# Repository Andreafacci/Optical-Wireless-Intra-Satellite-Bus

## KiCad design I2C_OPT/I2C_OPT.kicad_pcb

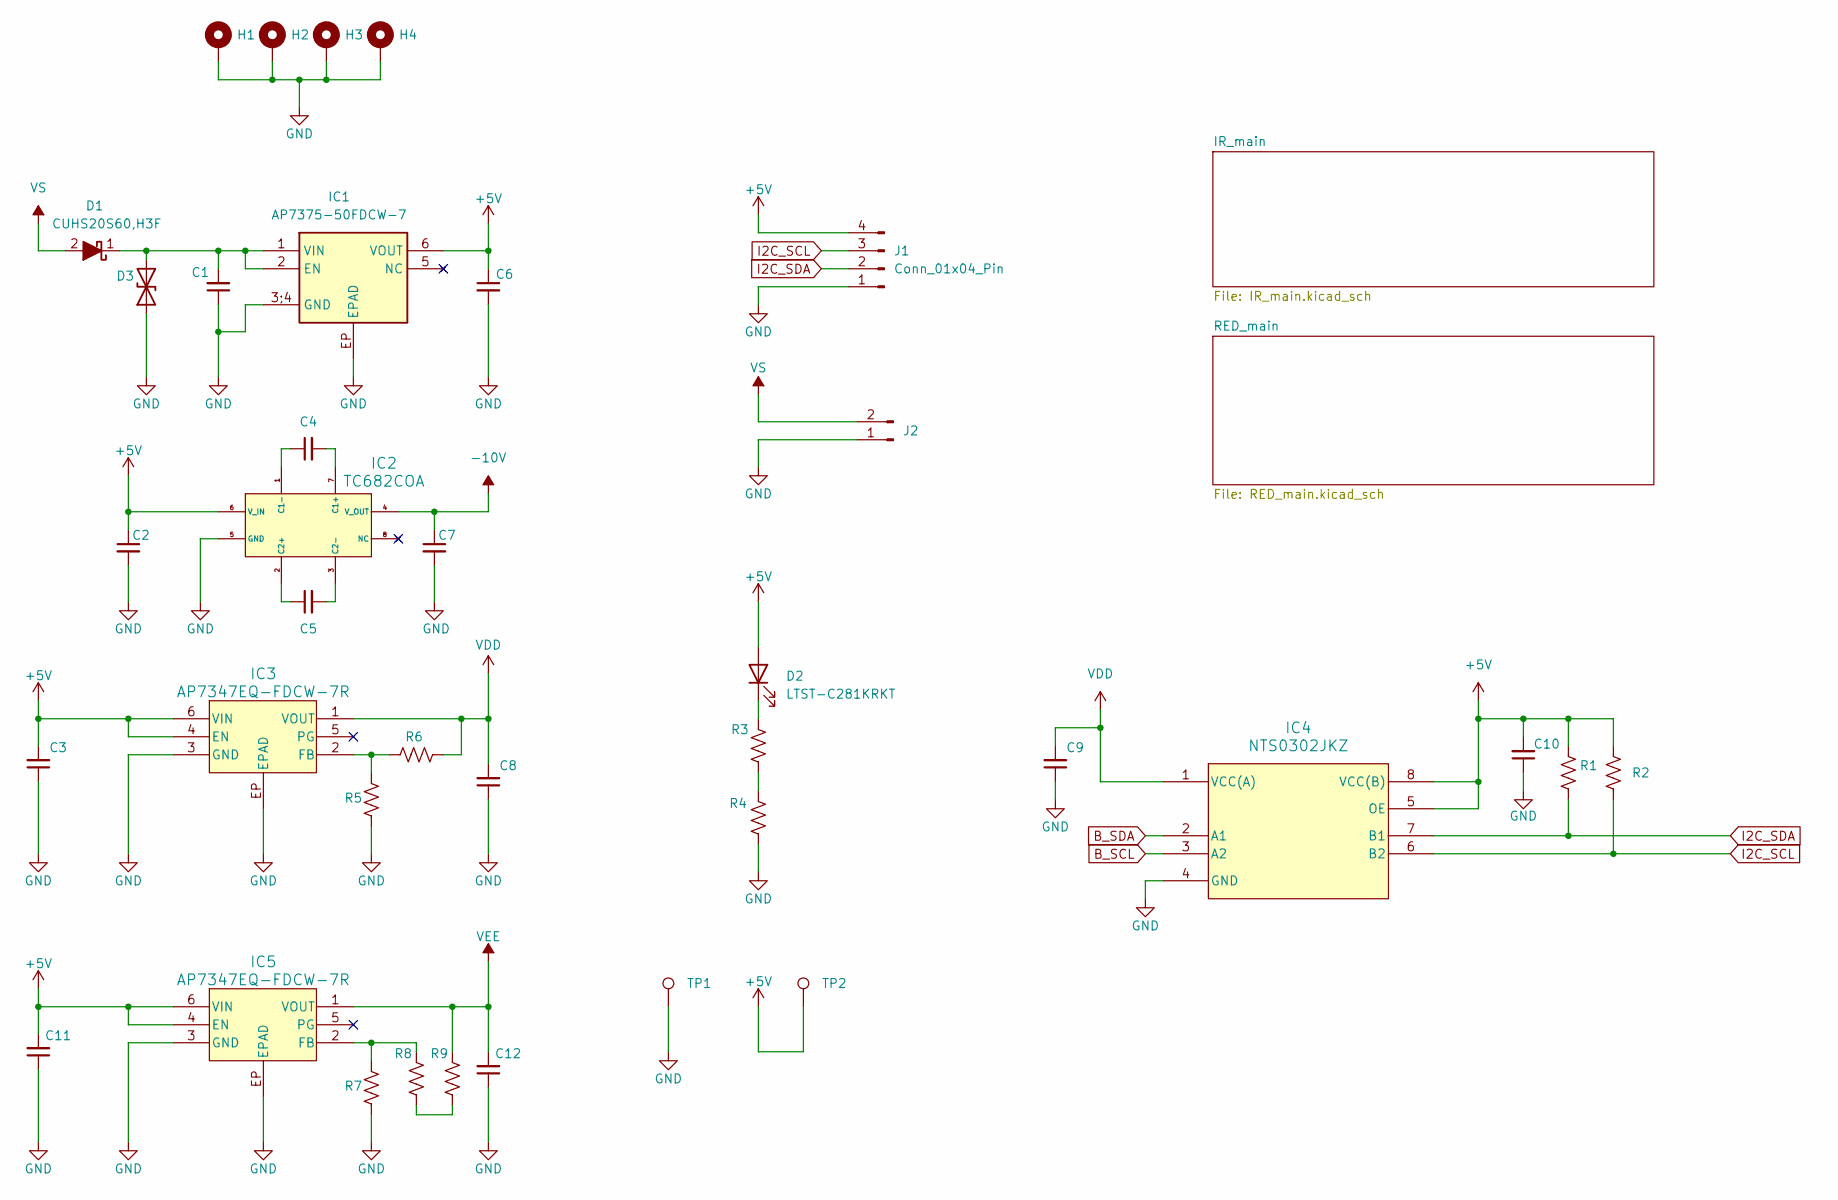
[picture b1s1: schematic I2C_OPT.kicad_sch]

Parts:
C1, C3, C4, C5, C8, C9, C10, C11, C12: C1005X5R1V105K050BC; C_0402_1005Metric
C2, C6, C7: CL10X106MO8NRNC; C_0603_1608Metric
D1: CUHS20S60,H3F; US2H; Mouser Part Number 757-CUHS20S60H3F
D2: LTST-C281KRKT; LED_0402_1005Metric
D3: 0402ESDA-MLP1; D_0402_1005Metric
H1, H2, H3, H4: MountingHole_Pad; MountingHole_2.2mm_M2_DIN965_Pad_TopBottom
IC1: AP7375-50FDCW-7; U-DFN2020-6; Mouser Part Number 621-AP7375-50FDCW-7
IC2: TC682COA; SOIC8-N_MC_MCH
IC3, IC5: AP7347EQ-FDCW-7R; U-DFN2020-6
IC4: NTS0302JKZ; X2SON08_1X1P4_NXP
J1: Conn_01x04_Pin; PinHeader_1x04_P2.54mm_Vertical
J2: PinHeader_1x02_P2.54mm_Vertical_GND
R1, R2: MCS0402MC1002FE000; R_0402_1005Metric
R3, R4: MCS04020D1200BE000; R_0402_1005Metric
R5: ERA-2AEB393X; R_0402_1005Metric
R6, R8, R9: ERA-2AEB8252X; R_0402_1005Metric
R7: MCS04020D4992BE000; R_0402_1005Metric
TP1, TP2: TestPoint; TestPoint_Pad_1.0x1.0mm

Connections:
+5V: C2.1, C3.2, C6.1, C10.2, C11.2, D2.2 (A), IC1.6 (VOUT), IC2.6 (V_IN), IC3.4 (EN), IC3.6 (VIN), IC4.5 (OE), IC4.8 (VCC(B)), IC5.4 (EN), IC5.6 (VIN), J1.4, R1.1, R2.1, TP2.1 (1_1); also elsewhere on the board
-10V: C7.1, IC2.4 (V_OUT); also elsewhere on the board
B_SCL: IC4.3 (A2); also elsewhere on the board
B_SDA: IC4.2 (A1); also elsewhere on the board
GND: C1.1, C2.2, C3.1, C6.2, C7.2, C8.1, C9.1, C10.1, C11.1, C12.1, D3.1 (A1), H1.1 (1_1), H2.1 (1_1), H3.1 (1_1), H4.1 (1_1), IC1.3 (GND), IC1.4 (GND), IC1.EP (EPAD), IC2.5 (GND), IC3.3 (GND), IC3.EP (EPAD), IC4.4 (GND), IC5.3 (GND), IC5.EP (EPAD), J1.1, J2.1, R4.1, R5.1, R7.1, TP1.1 (1_1); also elsewhere on the board
I2C_SCL: IC4.6 (B2), J1.3, R2.2
I2C_SDA: IC4.7 (B1), J1.2, R1.2
unnamed: C1.2, D1.1 (K), D3.2 (A2), IC1.1 (VIN), IC1.2 (EN)
unnamed: D2.1 (K), R3.2
unnamed: C4.2, IC2.7 (C1+)
unnamed: C4.1, IC2.1 (C1-)
unnamed: C5.1, IC2.2 (C2+)
unnamed: C5.2, IC2.3 (C2-)
unnamed: IC3.2 (FB), R5.2, R6.1
unnamed: IC5.2 (FB), R7.2, R8.2
unnamed: R3.1, R4.2
unnamed: R8.1, R9.1
VDD: C8.2, C9.2, IC3.1 (VOUT), IC4.1 (VCC(A)), R6.2
VEE: C12.2, IC5.1 (VOUT), R9.2; also elsewhere on the board
VS: D1.2 (A), J2.2

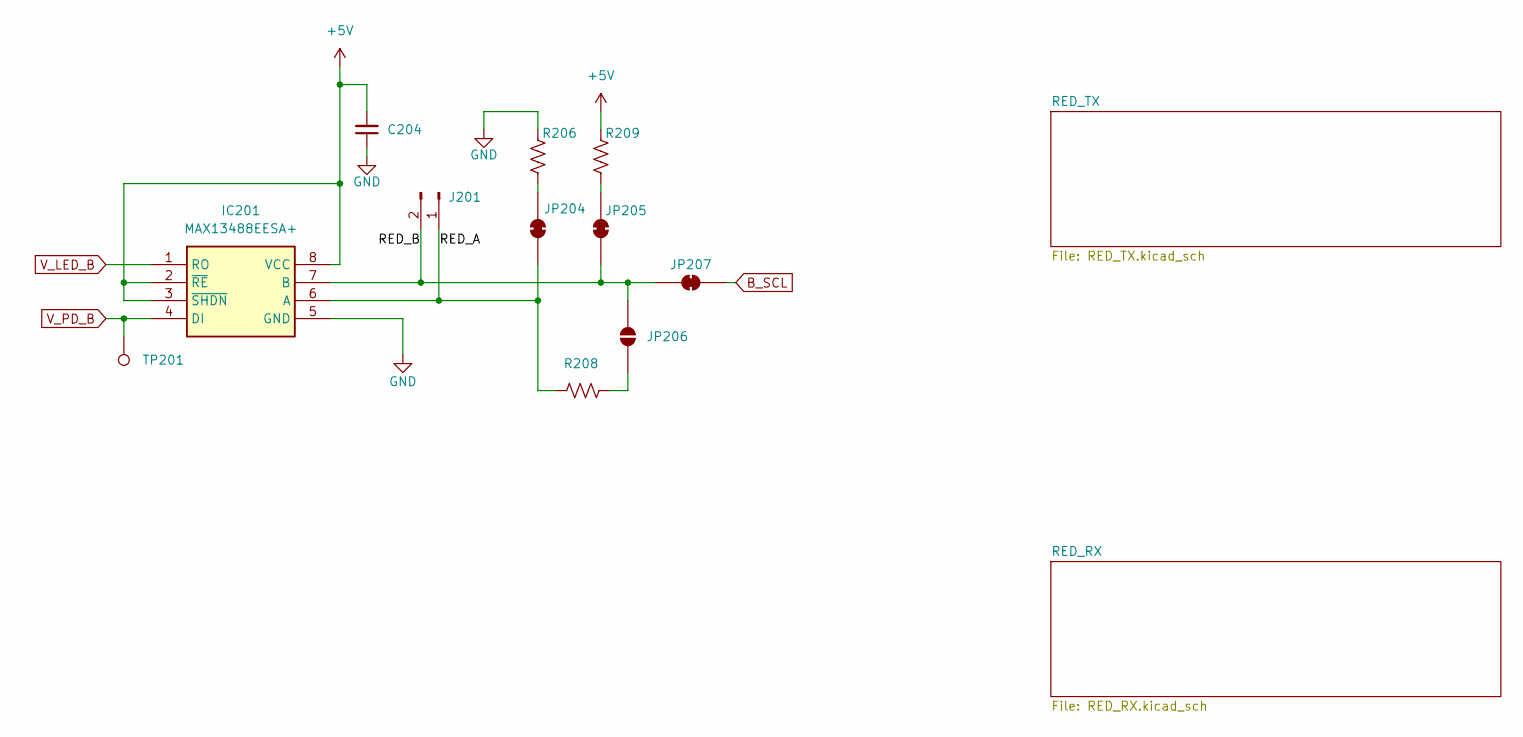
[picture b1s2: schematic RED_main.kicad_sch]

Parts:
C204: C1005X5R1V105K050BC; C_0402_1005Metric
IC201: MAX13488EESA+; SOIC127P600X175-8N; Mouser Part Number 700-MAX13488EESA
J201: PinHeader_1x02_P2.54mm_Vertical
JP204, JP205, JP207: SolderJumper_2_Bridged; SolderJumper-2_P1.3mm_Bridged_Pad1.0x1.5mm
JP206: SolderJumper_2_Open; SolderJumper-2_P1.3mm_Open_RoundedPad1.0x1.5mm
R206, R209: MCS04020C5601FE000; R_0402_1005Metric
R208: MCS04020D1200BE000; R_0402_1005Metric
TP201: TestPoint; TestPoint_Pad_1.0x1.0mm

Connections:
+5V: C204.2, IC201.2 (~RE), IC201.3 (~SHDN), IC201.8 (VCC), R209.1; also elsewhere on the board
/RED_main/RED_A: IC201.6 (A), J201.1, JP204.1 (A), R208.1
/RED_main/RED_B: IC201.7 (B), J201.2, JP205.1 (A), JP206.1 (A), JP207.2 (B)
B_SCL: JP207.1 (A); also elsewhere on the board
GND: C204.1, IC201.5 (GND), R206.1; also elsewhere on the board
unnamed: JP204.2 (B), R206.2
unnamed: JP205.2 (B), R209.2
unnamed: JP206.2 (B), R208.2
V_LED_B: IC201.1 (RO); also elsewhere on the board
V_PD_B: IC201.4 (DI), TP201.1 (1_1); also elsewhere on the board

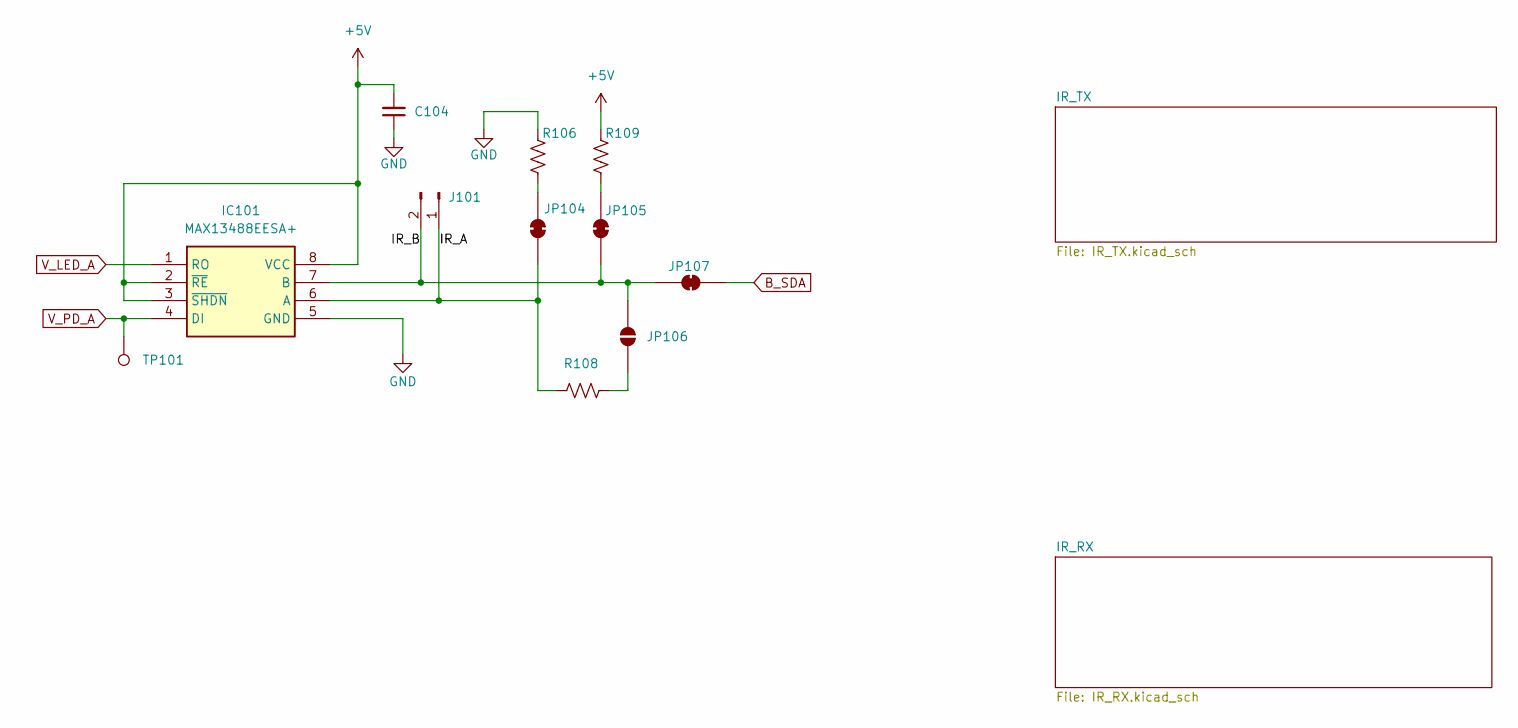
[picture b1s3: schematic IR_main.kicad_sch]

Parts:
C104: C1005X5R1V105K050BC; C_0402_1005Metric
IC101: MAX13488EESA+; SOIC127P600X175-8N; Mouser Part Number 700-MAX13488EESA
J101: PinHeader_1x02_P2.54mm_Vertical
JP104, JP105, JP107: SolderJumper_2_Bridged; SolderJumper-2_P1.3mm_Bridged_Pad1.0x1.5mm
JP106: SolderJumper_2_Open; SolderJumper-2_P1.3mm_Open_RoundedPad1.0x1.5mm
R106, R109: MCS04020C5601FE000; R_0402_1005Metric
R108: MCS04020D1200BE000; R_0402_1005Metric
TP101: TestPoint; TestPoint_Pad_1.0x1.0mm

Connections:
+5V: C104.2, IC101.2 (~RE), IC101.3 (~SHDN), IC101.8 (VCC), R109.1; also elsewhere on the board
/IR_main/IR_A: IC101.6 (A), J101.1, JP104.1 (A), R108.1
/IR_main/IR_B: IC101.7 (B), J101.2, JP105.1 (A), JP106.1 (A), JP107.2 (B)
B_SDA: JP107.1 (A); also elsewhere on the board
GND: C104.1, IC101.5 (GND), R106.1; also elsewhere on the board
unnamed: JP104.2 (B), R106.2
unnamed: JP105.2 (B), R109.2
unnamed: JP106.2 (B), R108.2
V_LED_A: IC101.1 (RO); also elsewhere on the board
V_PD_A: IC101.4 (DI), TP101.1 (1_1); also elsewhere on the board

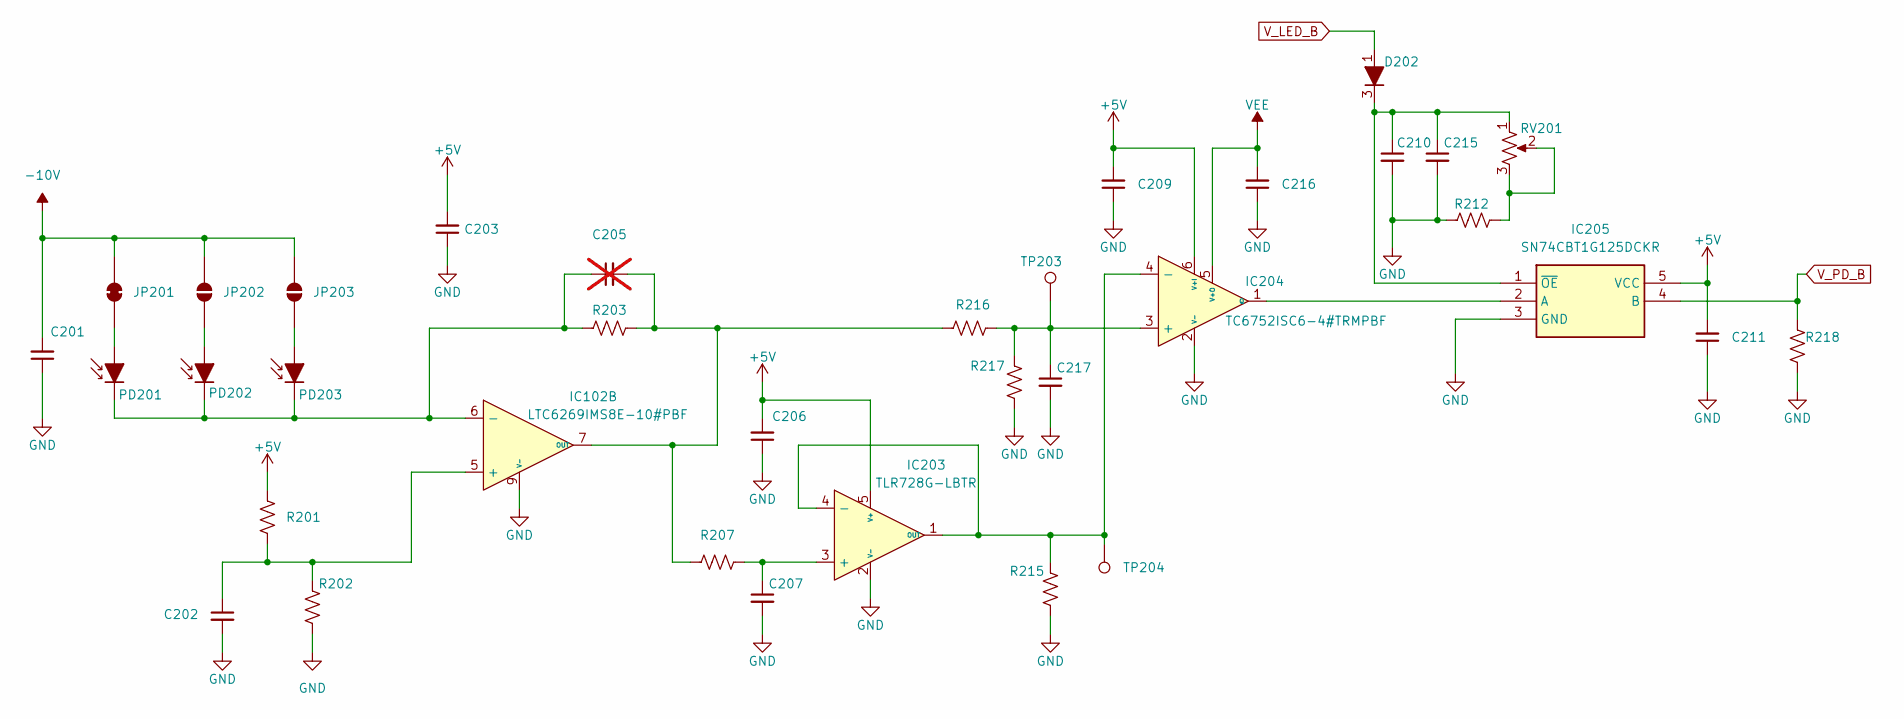
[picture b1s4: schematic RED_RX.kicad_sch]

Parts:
C201, C202, C203, C206, C209, C211, C216: C1005X5R1V105K050BC; C_0402_1005Metric
C205: 04023JR05ZBSTR\500; C_0402_1005Metric; not fitted
C207, C210, C215, C217: VJ0402A100FXACW1BC; C_0402_1005Metric
D202: 1SS193,LF; 1SS193LF; Mouser Part Number 757-1SS193LF
IC102: LTC6269IMS8E-10#PBF; SOP65P490X110-9N
IC203: TLR728G-LBTR; SOT23-5; Manufacturer_Part_Number TLR728G-LBTR
IC204: TC6752ISC6-4#TRMPBF; SC70-6; Mouser Part Number 584-LTC6752IS5TRMPBF
IC205: SN74CBT1G125DCKR; SOT65P210X110-5N; Mouser Part Number 595-SN74CBT1G125DBVR
JP201: SolderJumper_2_Bridged; SolderJumper-2_P1.3mm_Bridged_Pad1.0x1.5mm
JP202, JP203: SolderJumper_2_Open; SolderJumper-2_P1.3mm_Open_RoundedPad1.0x1.5mm
PD201: SFH 2240 A01; SFH2240A01
PD202: SFH 2713; SFH2713
PD203: SFH 2711 A01; SFH2711A01
R201, R203, R207: MCS04020C1004FE000; R_0402_1005Metric
R202, R215: MCS04020D4992BE000; R_0402_1005Metric
R212: MCS04020C5601FE000; R_0402_1005Metric
R216: MCS0402MC1002FE000; R_0402_1005Metric
R217: MCS04020C2703FE000
R218: ERA-2AEB8252X; R_0402_1005Metric
RV201: PVG5A204C03R00; PVG5A
TP203, TP204: TestPoint; TestPoint_Pad_1.0x1.0mm

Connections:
+5V: C203.2, C206.2, C209.2, C211.2, IC203.5 (V+), IC204.6 (V+I), IC205.5 (VCC), R201.2; also elsewhere on the board
-10V: C201.2, JP201.2 (B), JP202.2 (B), JP203.2 (B); also elsewhere on the board
GND: C201.1, C202.2, C203.1, C206.1, C207.2, C209.1, C210.2, C211.1, C215.2, C216.1, C217.2, IC102.9 (V-), IC203.2 (V-), IC204.2 (V-), IC205.3 (GND), R202.2, R212.1, R215.1, R217.2, R218.1; also elsewhere on the board
unnamed: C202.1, IC102.5 (+), R201.1, R202.1
unnamed: C205.1, IC102.6 (-), PD201.1 (K), PD202.1 (K), PD203.1 (K), R203.1
unnamed: C205.2, IC102.7 (OUT), R203.2, R207.2, R216.1
unnamed: C207.1, IC203.3 (+), R207.1
unnamed: IC203.1 (OUT), IC203.4 (-), IC204.4 (-), R215.2, TP204.1 (1_1)
unnamed: C217.1, IC204.3 (+), R216.2, R217.1, TP203.1 (1_1)
unnamed: IC204.1 (Q), IC205.2 (A)
unnamed: C210.1, C215.1, D202.3, IC205.1 (~OE), RV201.1
unnamed: JP201.1 (A), PD201.2 (A)
unnamed: JP202.1 (A), PD202.2 (A)
unnamed: JP203.1 (A), PD203.2 (A)
unnamed: R212.2, RV201.2, RV201.3
VEE: C216.2, IC204.5 (V+O); also elsewhere on the board
V_LED_B: D202.1; also elsewhere on the board
V_PD_B: IC205.4 (B), R218.2; also elsewhere on the board

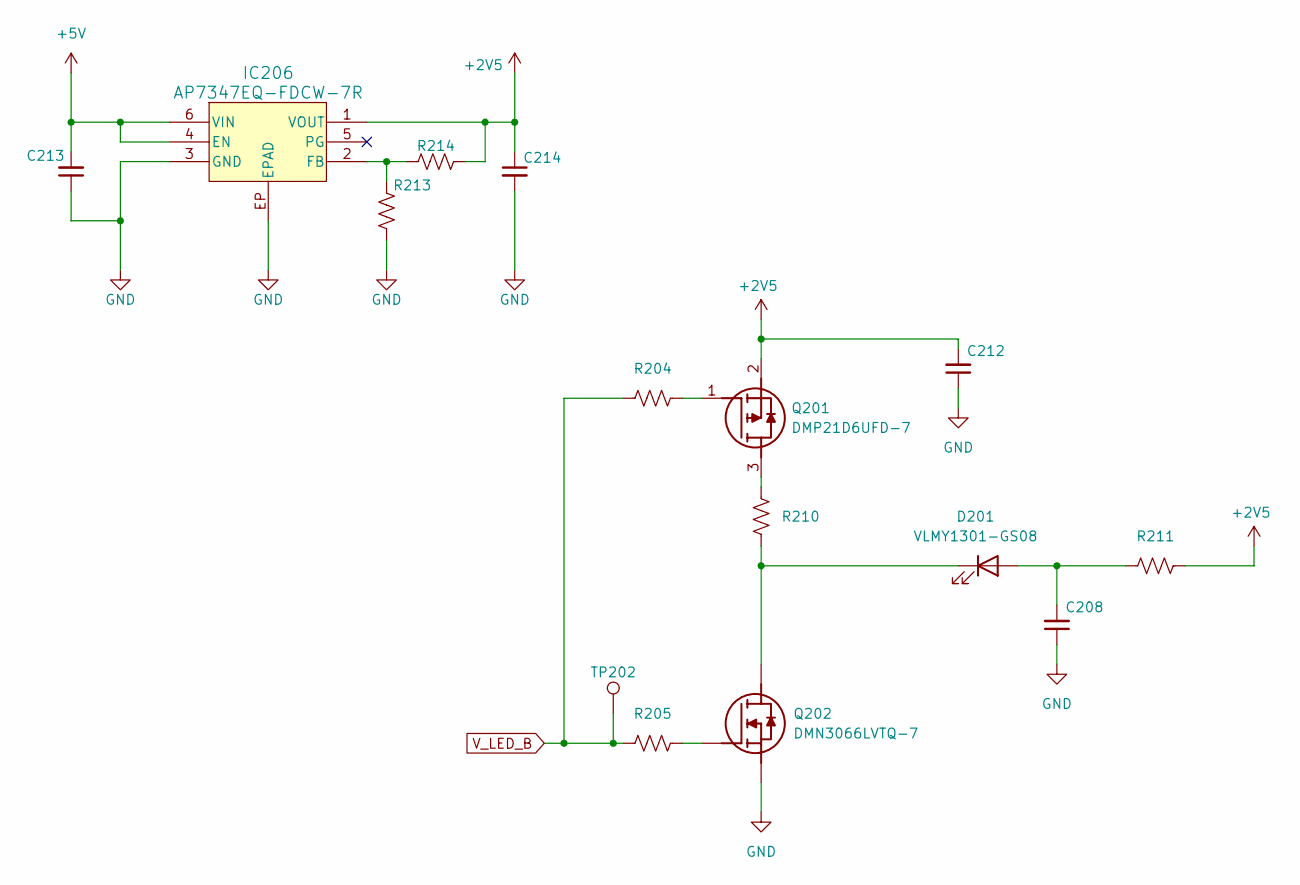
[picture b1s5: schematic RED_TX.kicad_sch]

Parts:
C208, C212, C213: C1005X5R1V105K050BC; C_0402_1005Metric
C214: CL10X106MO8NRNC; C_0603_1608Metric
D201: VLMY1301-GS08; LED_0603_1608Metric
IC206: AP7347EQ-FDCW-7R; U-DFN2020-6
Q201: DMP21D6UFD-7; DMP21D6UFD7; Mouser Part Number 621-DMP21D6UFD-7
Q202: DMN3066LVTQ-7; SOT95P280X100-6N; Mouser Part Number 757-SSM3J36FSLF
R204, R205, R211: CRCW06031R00FKEAHP; R_0603_1608Metric
R210: CRCW060310R0FKEAHP; R_0603_1608Metric
R213: MCS04020D4992BE000; R_0402_1005Metric
R214: ERA-2AEB9312X; R_0402_1005Metric
TP202: TestPoint; TestPoint_Pad_1.0x1.0mm

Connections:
+2V5: C212.2, C214.1, IC206.1 (VOUT), Q201.2 (S), R211.2, R214.2
+5V: C213.2, IC206.4 (EN), IC206.6 (VIN); also elsewhere on the board
GND: C208.1, C212.1, C213.1, C214.2, IC206.3 (GND), IC206.EP (EPAD), Q202.4 (S), R213.2; also elsewhere on the board
unnamed: C208.2, D201.2 (A), R211.1
unnamed: D201.1 (K), Q202.1 (D), Q202.2 (D), Q202.5 (D), Q202.6 (D), R210.2
unnamed: IC206.2 (FB), R213.1, R214.1
unnamed: Q201.3 (D), R210.1
unnamed: Q201.1 (G), R204.2
unnamed: Q202.3 (G), R205.2
V_LED_B: R204.1, R205.1, TP202.1 (1_1); also elsewhere on the board

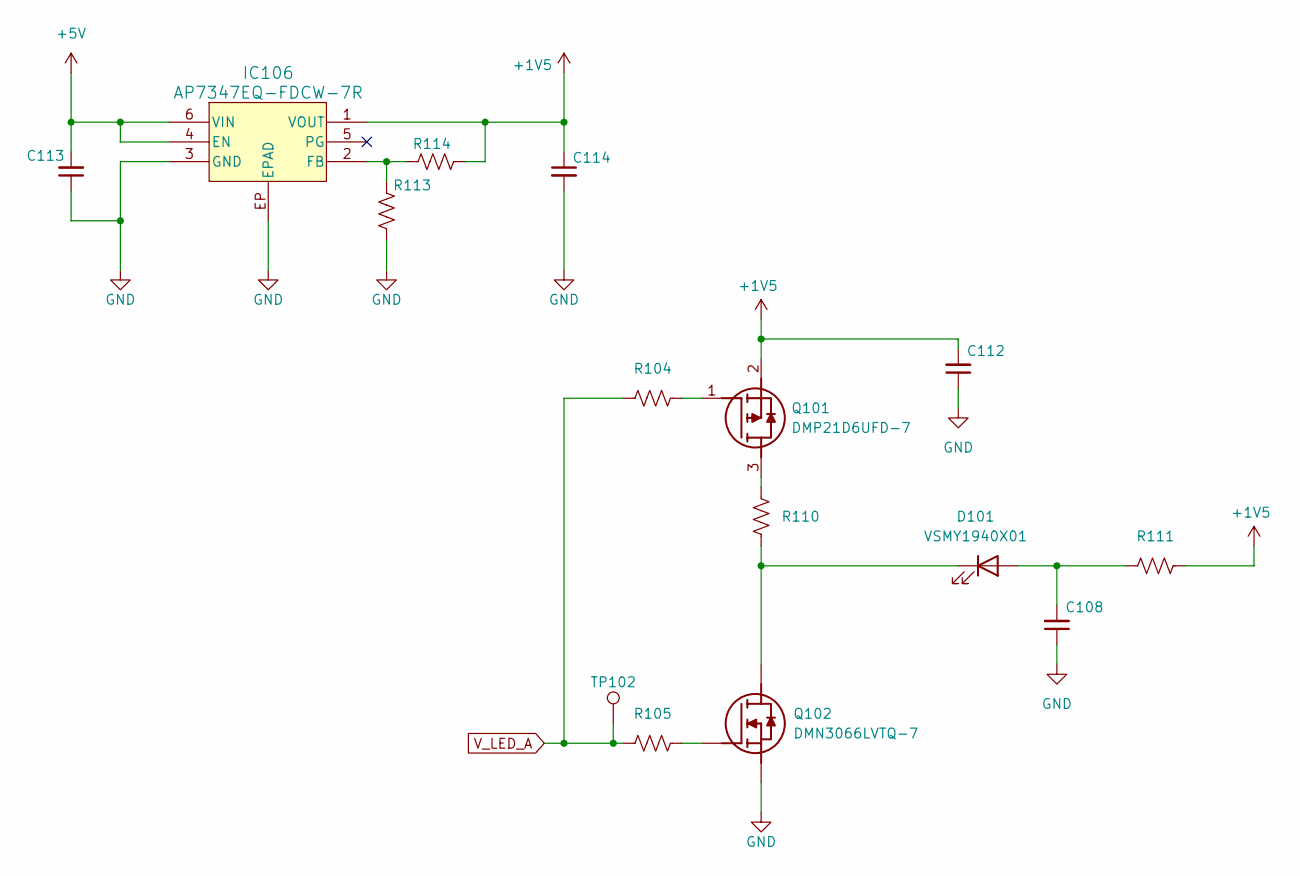
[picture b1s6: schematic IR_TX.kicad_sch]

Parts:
C108, C112, C113: C1005X5R1V105K050BC; C_0402_1005Metric
C114: CL10X106MO8NRNC; C_0603_1608Metric
D101: VSMY1940X01; LED_0805_2012Metric
IC106: AP7347EQ-FDCW-7R; U-DFN2020-6
Q101: DMP21D6UFD-7; DMP21D6UFD7; Mouser Part Number 621-DMP21D6UFD-7
Q102: DMN3066LVTQ-7; SOT95P280X100-6N; Mouser Part Number 757-SSM3J36FSLF
R104, R105, R111: CRCW06031R00FKEAHP; R_0603_1608Metric
R110: CRCW060310R0FKEAHP; R_0603_1608Metric
R113: MCS04020D4992BE000; R_0402_1005Metric
R114: RT0402BRD0744K2L; R_0402_1005Metric
TP102: TestPoint; TestPoint_Pad_1.0x1.0mm

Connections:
+1V5: C112.2, C114.1, IC106.1 (VOUT), Q101.2 (S), R111.2, R114.2
+5V: C113.2, IC106.4 (EN), IC106.6 (VIN); also elsewhere on the board
GND: C108.1, C112.1, C113.1, C114.2, IC106.3 (GND), IC106.EP (EPAD), Q102.4 (S), R113.2; also elsewhere on the board
unnamed: C108.2, D101.2 (A), R111.1
unnamed: D101.1 (K), Q102.1 (D), Q102.2 (D), Q102.5 (D), Q102.6 (D), R110.2
unnamed: IC106.2 (FB), R113.1, R114.1
unnamed: Q101.3 (D), R110.1
unnamed: Q101.1 (G), R104.2
unnamed: Q102.3 (G), R105.2
V_LED_A: R104.1, R105.1, TP102.1 (1_1); also elsewhere on the board

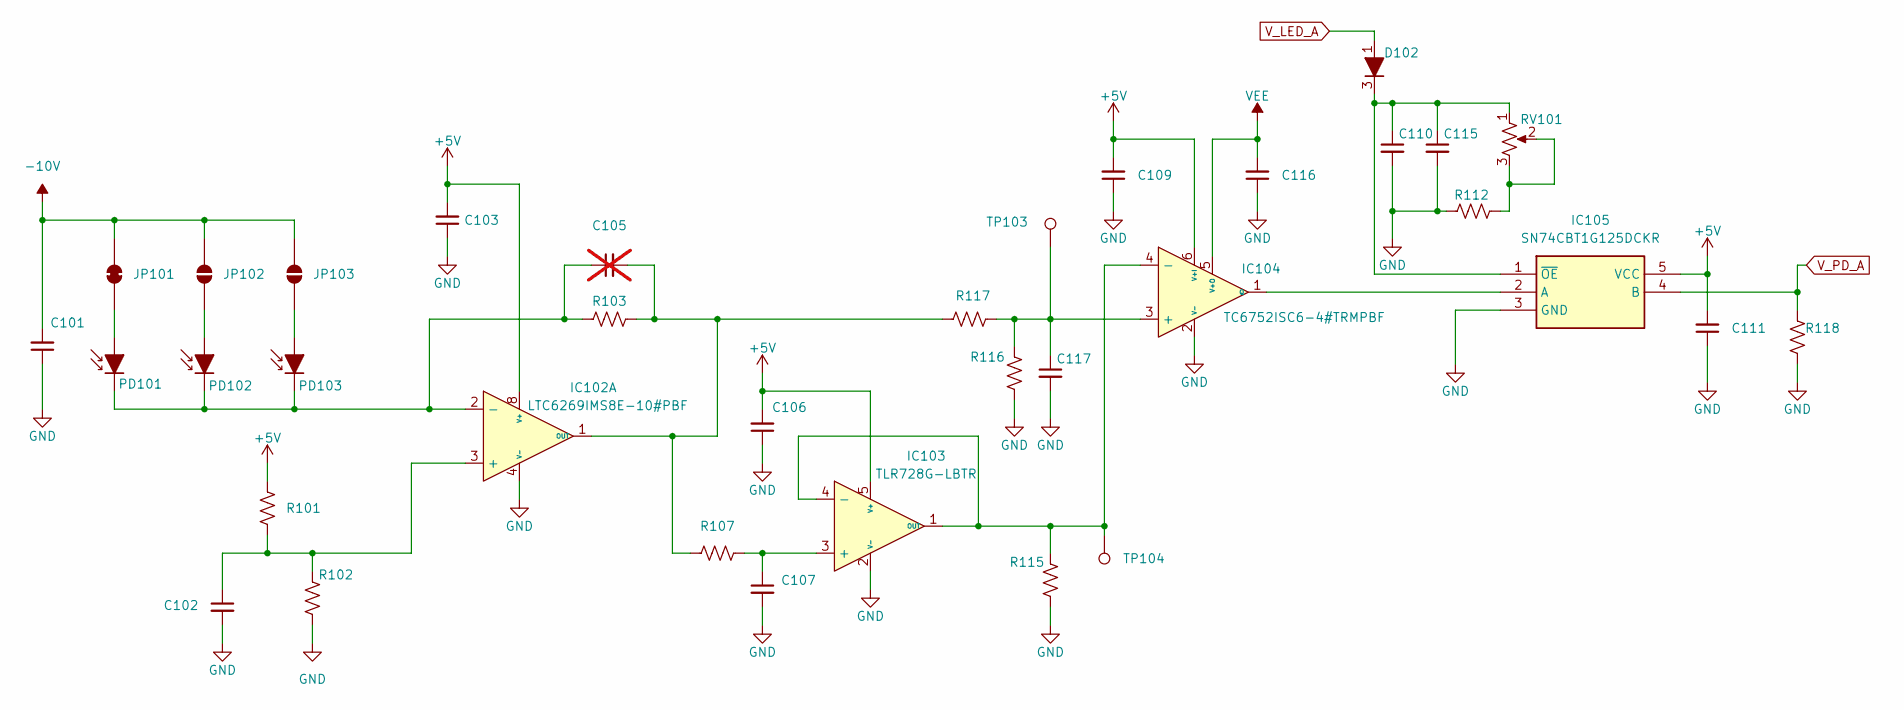
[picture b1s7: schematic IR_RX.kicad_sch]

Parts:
C101, C102, C103, C106, C109, C111, C116: C1005X5R1V105K050BC; C_0402_1005Metric
C105: 04023JR05ZBSTR\500; C_0402_1005Metric; not fitted
C107, C110, C115, C117: VJ0402A100FXACW1BC; C_0402_1005Metric
D102: 1SS193,LF; 1SS193LF; Mouser Part Number 757-1SS193LF
IC102: LTC6269IMS8E-10#PBF; SOP65P490X110-9N
IC103: TLR728G-LBTR; SOT23-5; Manufacturer_Part_Number TLR728G-LBTR
IC104: TC6752ISC6-4#TRMPBF; SC70-6; Mouser Part Number 584-LTC6752IS5TRMPBF
IC105: SN74CBT1G125DCKR; SOT65P210X110-5N; Mouser Part Number 595-SN74CBT1G125DBVR
JP101: SolderJumper_2_Bridged; SolderJumper-2_P1.3mm_Bridged_Pad1.0x1.5mm
JP102, JP103: SolderJumper_2_Open; SolderJumper-2_P1.3mm_Open_RoundedPad1.0x1.5mm
PD101: VEMD5110X01
PD102: VEMD6110X01; vemd6110x01
PD103: VEMD4110X01; D_0805_2012Metric
R101, R103, R107: MCS04020C1004FE000; R_0402_1005Metric
R102, R115: MCS04020D4992BE000; R_0402_1005Metric
R112: MCS04020C5601FE000; R_0402_1005Metric
R116: MCS04020C2703FE000
R117: MCS0402MC1002FE000; R_0402_1005Metric
R118: ERA-2AEB8252X; R_0402_1005Metric
RV101: PVG5A204C03R00; PVG5A
TP103, TP104: TestPoint; TestPoint_Pad_1.0x1.0mm

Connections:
+5V: C103.2, C106.2, C109.2, C111.2, IC102.8 (V+), IC103.5 (V+), IC104.6 (V+I), IC105.5 (VCC), R101.2; also elsewhere on the board
-10V: C101.2, JP101.2 (B), JP102.2 (B), JP103.2 (B); also elsewhere on the board
GND: C101.1, C102.2, C103.1, C106.1, C107.2, C109.1, C110.2, C111.1, C115.2, C116.1, C117.2, IC102.4 (V-), IC103.2 (V-), IC104.2 (V-), IC105.3 (GND), R102.2, R112.1, R115.1, R116.2, R118.1; also elsewhere on the board
unnamed: C102.1, IC102.3 (+), R101.1, R102.1
unnamed: C105.1, IC102.2 (-), PD101.1 (K), PD102.1 (K), PD103.1 (K), R103.1
unnamed: C105.2, IC102.1 (OUT), R103.2, R107.2, R117.1
unnamed: C107.1, IC103.3 (+), R107.1
unnamed: IC103.1 (OUT), IC103.4 (-), IC104.4 (-), R115.2, TP104.1 (1_1)
unnamed: C117.1, IC104.3 (+), R116.1, R117.2, TP103.1 (1_1)
unnamed: IC104.1 (Q), IC105.2 (A)
unnamed: C110.1, C115.1, D102.3, IC105.1 (~OE), RV101.1
unnamed: JP101.1 (A), PD101.2 (A)
unnamed: JP102.1 (A), PD102.2 (A)
unnamed: JP103.1 (A), PD103.2 (A)
unnamed: R112.2, RV101.2, RV101.3
VEE: C116.2, IC104.5 (V+O); also elsewhere on the board
V_LED_A: D102.1; also elsewhere on the board
V_PD_A: IC105.4 (B), R118.2; also elsewhere on the board

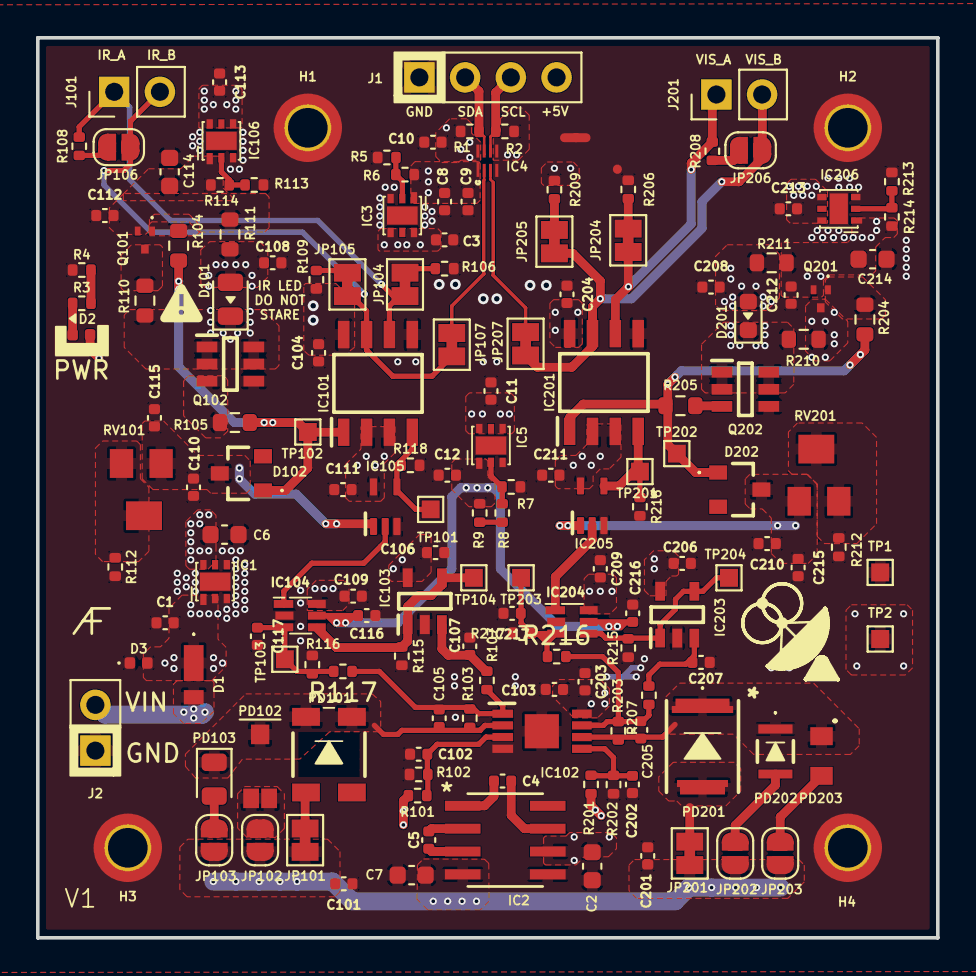
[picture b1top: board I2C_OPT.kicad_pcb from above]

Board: 2 copper layers, 50.0 x 50.0 mm, 158 parts (0 on the bottom side), 72 nets.
